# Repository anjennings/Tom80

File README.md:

# Tom80 - Z80 Based SBC

Several Versions of the Tom80 exist

## Version 2.0B

Specs:

	-See V2.0, differences listed here
	-400k usable ram 8x48k banks and 16k fixed common memory, CPU sees 64k at all times but lower 48k can be swapped around
	
	2B is the "definitive" version so all code going forward is designed for that version of the board.  
	Minor hardware differences mean that code for 2.0 may not work on 2.0B without tweaks (mostly related to ram banking)
	
Video about 2.0B (and its Operating Systems):
https://youtu.be/dH-JcmUzEUg

## Version 2.0

Specs:

	-Z80 CPU
	-32K EEPROM (0x0000 - 0x7FFF), Can be disabled for full SRAM memory space
	-64K SRAM (0x0000 - 0xFFFF)
	-16550 UART Controller
	-Counter Timer Chip (CTC) 
	-Parallel I/O Chip (PIO)
	-Parallax Propeller to allow for extra peripherals
		-SD Card
		-VGA 
		-PS/2 Keyboard
	-5V Power Via USB (Z80 Only)
	-Regulated power via wall jack (Z80 and Propeller)
	
	V2 is 99% compatable with V1.X so most (if not all) code can be ported without much trouble
	There are several (minor) known issues with V2 that will likely be fixed in a future revision
	
See a video about Version 2.0 here:
https://youtu.be/p65Hw1WCuoc

## Version 1.X

Specs:

	-Z80 CPU
	-32 Kilobytes EEPROM (0x0000 - 0x7FFF)
	-32 Kilobytes SRAM (0x8000 - 0xFFFF)
	-16550 UART Controller
	-USB Serial Interface
	
	A memory monitor (ASH.asm) can be assembled and run
	Varoious flavors of basic can also be ported
	
See a video about Version 1.1 here:
https://youtu.be/3KAjZbjPqnA
	
## Prototype

Specs:

	-Z80 CPU
	-2 Kilobytes EEPROM (0x0000 - 0x07FF)
	-2 Kilobytes SRAM (0x0800 - 0x0FFF)
	-A single 8 bit latch for I/O

See a video of the prototype here:
https://www.youtube.com/watch?v=QeUG9fH5Wn8

Was disassembled in late 2020, lives on only in pictures and videos

## Other Stuff

Also Includes:

	-Custom EEPROM Programmer Schematics
		-ATMEGA32A
		-28 Pin ZIF Socket
		-USB Interface
		
See a video about the programmer here:
https://youtu.be/HartpD7Tr4I

Other (Older) files:

	Arduino Micro EEPROM Programmer (Predecessor to Custom Programmer)
		-Arduino Code
		-Script to send data via Seral
	
	Various Programs, mostly tests for EEPROM, SRAM, and I/O
	
## TODO (As of 2021-10-9)

	Tests for CTC are still lacking
	Firmware for Propeller is not optimized
	Schematics and manufacturing files for V2/V2B
	Better documentation in general
	Makefiles
	Photos of 2B
	Finish FUZIX port

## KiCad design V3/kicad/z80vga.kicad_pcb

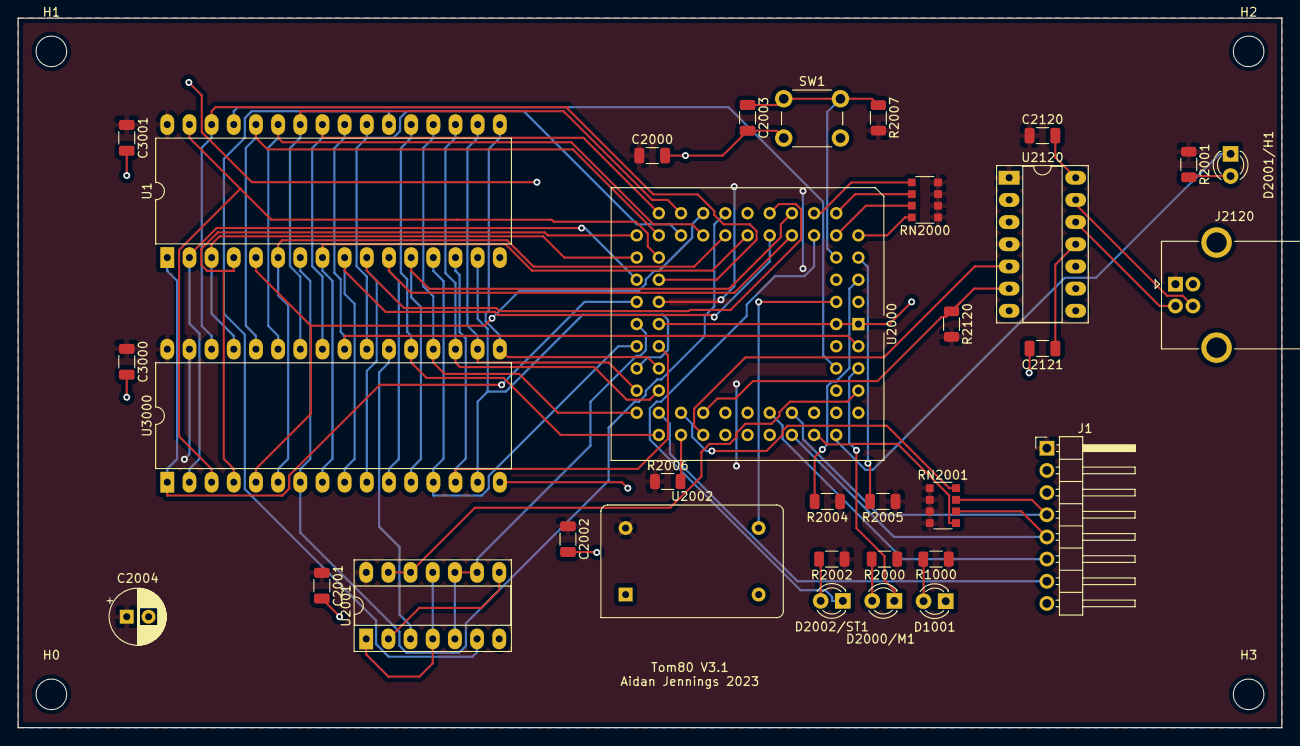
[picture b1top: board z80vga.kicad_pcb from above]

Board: 2 copper layers, 144.8 x 81.3 mm, 37 parts (0 on the bottom side), 64 nets.

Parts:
C2000, C2001, C2002, C2003, C3000, C3001: 22pf; C_1206_3216Metric
C2004: 1uF; CP_Radial_D6.3mm_P2.50mm
C2120, C2121: 22pF; C_1206_3216Metric
D1001, D2000/M1, D2001/H1, D2002/ST1: LED; LED_D3.0mm
H0, H1, H2, H3: MountingHole; MountingHole_3.5mm
J1: Conn_01x08_Male; PinHeader_1x08_P2.54mm_Horizontal
J2120: USB_B; USB_B_OST_USB-B1HSxx_Horizontal
R1000: 2.2K; R_1206_3216Metric
R2000, R2001, R2002, R2004, R2005, R2006, R2007: R; R_1206_3216Metric
R2120: 100k; R_1206_3216Metric
RN2000, RN2001: 4 x 10K; R_Array_Convex_4x1206
SW1: SW_Push; SW_PUSH_6mm
U1: AS6C4008-55PCN; DIP-32_W15.24mm_LongPads
U2000: Z8-L180-S180-180-PLCC-68; PLCC-68_THT-Socket
U2001: 74HCT00; DIP-14_W7.62mm_Socket_LongPads
U2002: 14.7456 MHz; Oscillator_DIP-14
U2120: MCP2221AxP; DIP-14_W7.62mm_Socket_LongPads
U3000: SST39SF040; DIP-32_W15.24mm_LongPads

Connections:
+5V: C2000.1, C2001.1, C2002.1, C2004.1, C2120.1, C3000.1, C3001.1, J1.1, J2120.1, R1000.2, R2000.1, R2001.1, R2002.1, R2004.1, R2005.1, R2006.1, R2007.2, R2120.2, RN2000.1, RN2000.2, RN2000.3, RN2000.4, RN2001.1, RN2001.2, RN2001.3, RN2001.4, U1.32, U2000.34, U2001.14, U2002.14, U2120.1, U2120.4, U3000.31, U3000.32
/2000_CPU/A0: U1.12, U2000.14, U3000.12
/2000_CPU/A1: U1.11, U2000.15, U3000.11
/2000_CPU/A2: U1.10, U2000.16, U3000.10
/2000_CPU/A3: U1.9, U2000.17, U3000.9
/2000_CPU/A4: U1.8, U2000.19, U3000.8
/2000_CPU/A5: U1.7, U2000.20, U3000.7
/2000_CPU/A6: U1.6, U2000.21, U3000.6
/2000_CPU/A7: U1.5, U2000.22, U3000.5
/2000_CPU/A8: U1.27, U2000.23, U3000.27
/2000_CPU/A9: U1.26, U2000.24, U3000.26
/2000_CPU/A10: U1.23, U2000.25, U3000.23
/2000_CPU/A11: U1.25, U2000.26, U3000.25
/2000_CPU/A12: U1.4, U2000.27, U3000.4
/2000_CPU/A13: U1.28, U2000.28, U3000.28
/2000_CPU/A14: U1.3, U2000.29, U3000.29
/2000_CPU/A15: U1.31, U2000.30, U3000.3
/2000_CPU/A16: U1.2, U2000.31, U3000.2
/2000_CPU/A17: U1.30, U2000.32, U3000.30
/2000_CPU/A18: U1.1, U2000.33, U3000.1
/2000_CPU/A19: U2000.35, U2001.5, U2001.9, U2001.10
/2000_CPU/BUSREQ: R2005.2, U2000.7
/2000_CPU/CKS: J1.4, RN2001.7, U2000.57
/2000_CPU/CLK: U2000.4, U2002.8
/2000_CPU/CTS0: R2006.2, U2000.46
/2000_CPU/C_RST: C2003.1, R2007.1, SW1.1, U2000.8
/2000_CPU/D0: U1.13, U2000.37, U3000.13
/2000_CPU/D1: U1.14, U2000.38, U3000.14
/2000_CPU/D2: U1.15, U2000.39, U3000.15
/2000_CPU/D3: U1.17, U2000.40, U3000.17
/2000_CPU/D4: U1.18, U2000.41, U3000.18
/2000_CPU/D5: U1.19, U2000.42, U3000.19
/2000_CPU/D6: U1.20, U2000.43, U3000.20
/2000_CPU/D7: U1.21, U2000.44, U3000.21
/2000_CPU/DCD0: RN2001.8, U2000.47
/2000_CPU/DREQ1: RN2001.5, U2000.58
/2000_CPU/HALT: D2001/H1.1, U2000.60
/2000_CPU/INT0: RN2000.6, U2000.10
/2000_CPU/INT1: RN2000.7, U2000.11
/2000_CPU/INT2: RN2000.5, U2000.12
/2000_CPU/M1: D2000/M1.1, U2000.65
/2000_CPU/MREQ: U2000.63, U2001.12, U2001.13
/2000_CPU/NMI: RN2000.8, U2000.9
/2000_CPU/RAM_CS: U1.22, U2001.6
/2000_CPU/RD: U1.24, U2000.67, U3000.24
/2000_CPU/ROM_CS: U2001.3, U3000.22
/2000_CPU/RTS0: J1.7, U2000.45
/2000_CPU/RX: R2120.1, U2000.49, U2120.6
/2000_CPU/RXS: J1.5, RN2001.6, U2000.56
/2000_CPU/ST: D2002/ST1.1, U2000.13
/2000_CPU/TX: U2000.48, U2120.5
/2000_CPU/TXS: J1.6, U2000.55
/2000_CPU/WAIT: R2004.2, U2000.5
/2000_CPU/WR: U1.29, U2000.66
GND: C2000.2, C2001.2, C2002.2, C2003.2, C2004.2, C2120.2, C2121.2, C3000.2, C3001.2, D1001.1, J1.3, J2120.4, J2120.5, SW1.2, U1.16, U2000.1, U2000.2, U2000.18, U2000.36, U2001.7, U2002.7, U2120.14, U3000.16
unnamed: C2121.1, U2120.11
unnamed: D1001.2, R1000.1
unnamed: D2000/M1.2, R2000.2
unnamed: D2001/H1.2, R2001.2
unnamed: D2002/ST1.2, R2002.2
unnamed: J2120.2, U2120.12
unnamed: J2120.3, U2120.13
unnamed: U2001.1, U2001.4, U2001.11
unnamed: U2001.2, U2001.8

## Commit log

2020-04-15 got EEPROM programmer working
2020-04-22 removed old project files
2020-08-20 updated readme and removed old files
2020-08-29 added source code for projects
2020-09-10 added ash.asm
2020-09-10 added schematics
2020-09-28 added schematic for custom EEPROM Programmer
2020-09-28 added video link
2020-10-07 Finally got around to the programmer
2020-10-09 added SRAM stuff
2020-10-10 Added more to monitor
2020-10-11 I think the UART should be correct now
2020-10-14 started working on a buffer
2020-10-20 reworked the tokenizer loop
2020-10-20 did some cleanup
2020-10-20 I should be sleeping and not writing a parser
2020-10-21 created generic tokenize instruction sr
2020-10-21 Wrote parse literal function, still mostly untested
2020-10-22 literal parser should now save to parser memory
2020-10-22 Parser ALMOST works, the rotations are still buggy
2020-10-22 stupid carry bits
2020-10-22 Started adding the execution subroutine
2020-11-15 Sent away for the PCBs
2020-12-19 big updates since last time
2020-12-19 it kinda sorta works most of the time
2020-12-23 execution instructions should now execute (and return!)
2020-12-26 reorganized file structure
2020-12-26 Updated a bunch of files, added write action to monitor
2020-12-26 updated monitor
2020-12-30 it kinda boots!
2020-12-31 it talks!
2021-01-02 created script to send basic programs via serial
2021-01-02 added photos of completed boards and some of the prototypes
2021-01-03 changed some of the source code to be compatable with different assemblers
2021-01-05 added zalloc
2021-01-05 trim should now work for zalloc
2021-01-06 memory can be allocated in small amounts, but not freed
2021-01-06 The first tests worked
2021-01-08 memory allocation still needs some work
2021-01-09 started writing code via z88dk
2021-01-10 printstr works!
2021-01-15 migrated most of the tom80 code to z88dk
2021-01-15 minor touch ups to code
2021-01-17 ill make my own computer, withblackjack and pointers
2021-01-19 time to learn the precompiler i guess
2021-01-24 tried to get stdio to work, went back to rebuilding the parser
2021-02-05 just missing a few bits of functionality
2021-02-06 updated c parser
2021-02-08 I got bored and wrote the mandlebrot seq, Ill port it to z80 later
2021-02-08 it kinda looks like it again now
2021-02-09 after much fine tuning...
2021-02-24 started on quickload and a whole bunch of other stuff
2021-02-25 Added script to trim files before sending
2021-03-19 tinkering with quickload still
2021-03-19 Final Version of Programmer Schematic
2021-05-17 Added files related to testing version 2
2021-05-17 Reorganizing files
2021-05-17 added photo of partly assembled V2
2021-05-17 update readme with picture
2021-05-17 updated readme files
2021-05-21 Tests for peripherals
2021-05-22 PIO Communication Test
2021-05-22 added readme to V2 folder
2021-05-22 markdown is finicky
2021-05-23 PIO Bidirectional Test seems to be working now...
2021-05-23 Created dumb terminal test for Prop
2021-05-23 ASH VGA has drivers to print text to screen
2021-05-26 Monitor now detects if propeller is active on boot
2021-05-27 Turns out that debug text takes a lot of time and space
2021-05-27 Documentation updates
2021-05-27 Bidirectional data is finally working!
2021-05-29 Created PS2 Test and CPM Disk init routine for SD card
2021-05-29 Added more disk routines
2021-05-31 Reorganized ASH for pasmo compiler
2021-05-31 Reorganized CPM source code and added a readme
2021-05-31 Documentation and Directory Cleanup
2021-05-31 Created utility to merge multiple binaries into one
2021-06-01 Updated TinyBasic code to run alone or following the monitor
2021-06-01 Created CPM bootloader
2021-06-02 Slowly debugging the CPM boot process
2021-06-02 CPM BOOTS!
2021-06-02 Ok, NOW it boots
2021-06-03 Added SD card check
2021-06-03 switched from printf to print
    absolutely atrocious libraries, printf doesn't work sometimes
2021-06-03 Writes still aren't committing but the protocol is there
2021-06-03 writes are working now!
2021-06-04 Weeding out the bugs in CPM
2021-06-05 CPM still has issues but less crashes than before
2021-06-05 Minor Fixes
2021-06-06 Seems to be booting into BASIC now, so thats a good sign
2021-06-06 Updated R/W process for disk
2021-06-06 Added prop support for Drive B:
2021-06-06 Added a second drive to BIOS, still needs testing
2021-06-06 Updated README docs
2021-06-07 Drive A: and B: can now be accesses via CPM
2021-06-09 Drive A, B, and C are now available
2021-06-09 Ok not sure what that was all about
    everything SEEMS to work now...
2021-06-11 Minor cleanup, removing unneeded code segments
2021-06-11 Removing more unneeded code
2021-06-11 Reads should now take significantly less time
2021-06-19 Expanded main disk size
2021-06-26 No reason not to treat the disks like they have the maximum number of tracks
2021-07-24 Its not working, no surprise
2021-08-19 removed VGA core from propeller firmware
2021-08-26 updated Makefiles, everything still works
2021-08-27 simplified the Kernel copying process
2021-08-27 No need to give 4k of ROM to a 23 byte bootloader
2021-09-11 2.0B works! Began on fuzix bootloader
2021-10-09 Fixed several bugs related to FUIZX development
2021-10-09 Added fuzix files
2021-10-09 Updated documentation
2021-10-12 Still troubleshooting pio drivers
2021-10-16 disk io now runs without halts
2021-12-18 Updated readme file
2022-02-05 Added kicad files
2022-02-09 probably going to split into two boards
2022-04-12 Copied GAL files
2022-04-12 updated GAL makefile
2022-04-12 Updated GAL Logic
2022-04-16 Updated GAL logic for different ROM chip
2022-04-28 Updated PCB files
2022-05-05 fixing up CPU page and routing
2022-05-07 Fixed a few USB/UART issues
2022-05-14 Still putting final touches on CPU page
2022-05-14 altered logic to reflect schematic
2022-05-14 Hopefully the last major changes to the CPU
2022-05-14 last touches on peripherals and memory
2022-05-14 Cleaned up a few more pages
2022-05-14 new footprints and fixed reset routes
2022-05-14 last changes before autoroute
2022-05-14 minor changes to make routing easier
2022-05-16 still trying to make routes work
2022-05-16 fixed up PIO routing
2022-05-16 more PIO routing
2022-05-16 routing SD card control signals
2022-05-16 Peripherals are routed
2022-05-16 rerouted uart signals
2022-05-16 Completely redesigned board layout
2022-05-16 totally redid board layout
2022-05-16 SPI peripherals routed
2022-05-16 ran autoroute
2022-05-20 routed memory and some control signals
2022-05-20 autoroute complete
2022-05-28 Final checks and DRC
2022-05-28 added silkscreen text
2022-05-29 generated gerber files
2022-05-30 generated pdf of schematic
2022-05-30 3.0 planning (#7)
    * Added kicad files
    * probably going to split into two boards
    * Copied GAL files
    * Delete TODO.md
    * updated GAL makefile
    * Updated GAL Logic
2022-05-30 3.0 planning no header (#8)
    * Added kicad files
    * probably going to split into two boards
    * Copied GAL files
    * Delete TODO.md
    * updated GAL makefile
    * Updated GAL Logic
2022-06-12 moved EEPROM files to /old
2022-06-20 Reworking 3.0 board
2022-06-20 changed footprint on RAM chip
2022-06-20 cleared out old memory traces
2022-06-20 started on rerouting
2022-06-20 on to autoroute
2022-06-20 little more cleanup
2022-06-20 more cleanup
2022-06-20 ill let the autoroute do the rest
2022-06-20 reroute complete
2022-06-21 made PQFP leads fatter
2022-06-22 Design Rule Check
2022-06-22 Minor pcb touch up
2022-06-26 gerber files
2022-07-31 just totally redid the whole thing
2022-08-06 More rearranging
2022-08-07 added a few caps
2022-08-07 Routed ROM and RAM together
2022-08-08 Working on tinybasic port
2022-08-08 tinyBasic port
2022-08-10 more routing
2022-08-14 more routes
2022-11-24 A lot of disorganized changes
2022-11-24 Updated SPI to use CPU signals
    8 bit register chip controls CS lines
2022-11-24 Renamed and added caps to SD page
2022-11-24 Cleanup
2022-11-24 3.1 CSIO SPI Bus (#9)
    * Updated SPI to use CPU signals
    8 bit register chip controls CS lines
    * Renamed and added caps to SD page
    * Cleanup
2022-11-24 First two R arrays
2022-11-24 Added one more r array
2022-11-24 added cap for SPI FF
2022-11-24 3.1 Resistor Replacement (#10)
    * First two R arrays
    * Added one more r array
    * added cap for SPI FF
2022-11-24 Extended cpu pads
2022-11-24 Extended cpu pads (#12)
2022-11-24 Fixed Schematic Heirarchy issue
2022-11-24 some footprints re-added to board
2022-11-25 Add footprints added
2022-11-25 Minor changes
2022-11-25 3.1 fix sheet hierarchy (#13)
    * Fixed Schematic Heirarchy issue
    * some footprints re-added to board
    * Add footprints added
    * Minor changes
2022-11-25 moved all crtyd lines to same place in file
2022-11-25 Duplicate lines were causing issues
2022-11-25 3.1 redraw cpu courtyard (#14)
    * moved all crtyd lines to same place in file
    * Duplicate lines were causing issues
2022-11-30 Added pin header for SPI lines
2022-11-30 routed last of non-bus lines
2022-12-20 attempted to route memory lines
2022-12-20 Added new symbol and footprint
2022-12-20 CTS0 no longer drives an LED
2022-12-20 Final cleanup before memory routing
2022-12-20 got CTS0 and RTS mixed up
2022-12-20 Removed extra led from board
2022-12-20 Updated signature
2023-10-28 small changes
2023-10-28 3 1 1 m memory (#15)
    * moved EEPROM files to /old
    * Reworking 3.0 board
    * changed footprint on RAM chip
    * cleared out old memory traces
    * started on rerouting
    * on to autoroute
2023-10-28 Replace chip with PLCC, strip out uncritical elements
2023-10-28 new board layout, not routing yet, still need to check schematics
2023-11-04 updated pcbs some more
2023-11-04 Replace reset with simpler circuit
2023-11-04 replace GAL with 74 series logic
2023-11-04 rearranged pcb a bit
2023-11-18 finalize board layout, just need to route
2023-11-18 easy routes are done
2023-11-18 double checked CPU signals
2023-11-18 regen netlist
2023-11-19 moved resistor array
2023-11-19 final routes
2023-11-24 final, minor fixes
2023-11-24 missed one unconnected
2023-11-24 generated gerber and drill files
